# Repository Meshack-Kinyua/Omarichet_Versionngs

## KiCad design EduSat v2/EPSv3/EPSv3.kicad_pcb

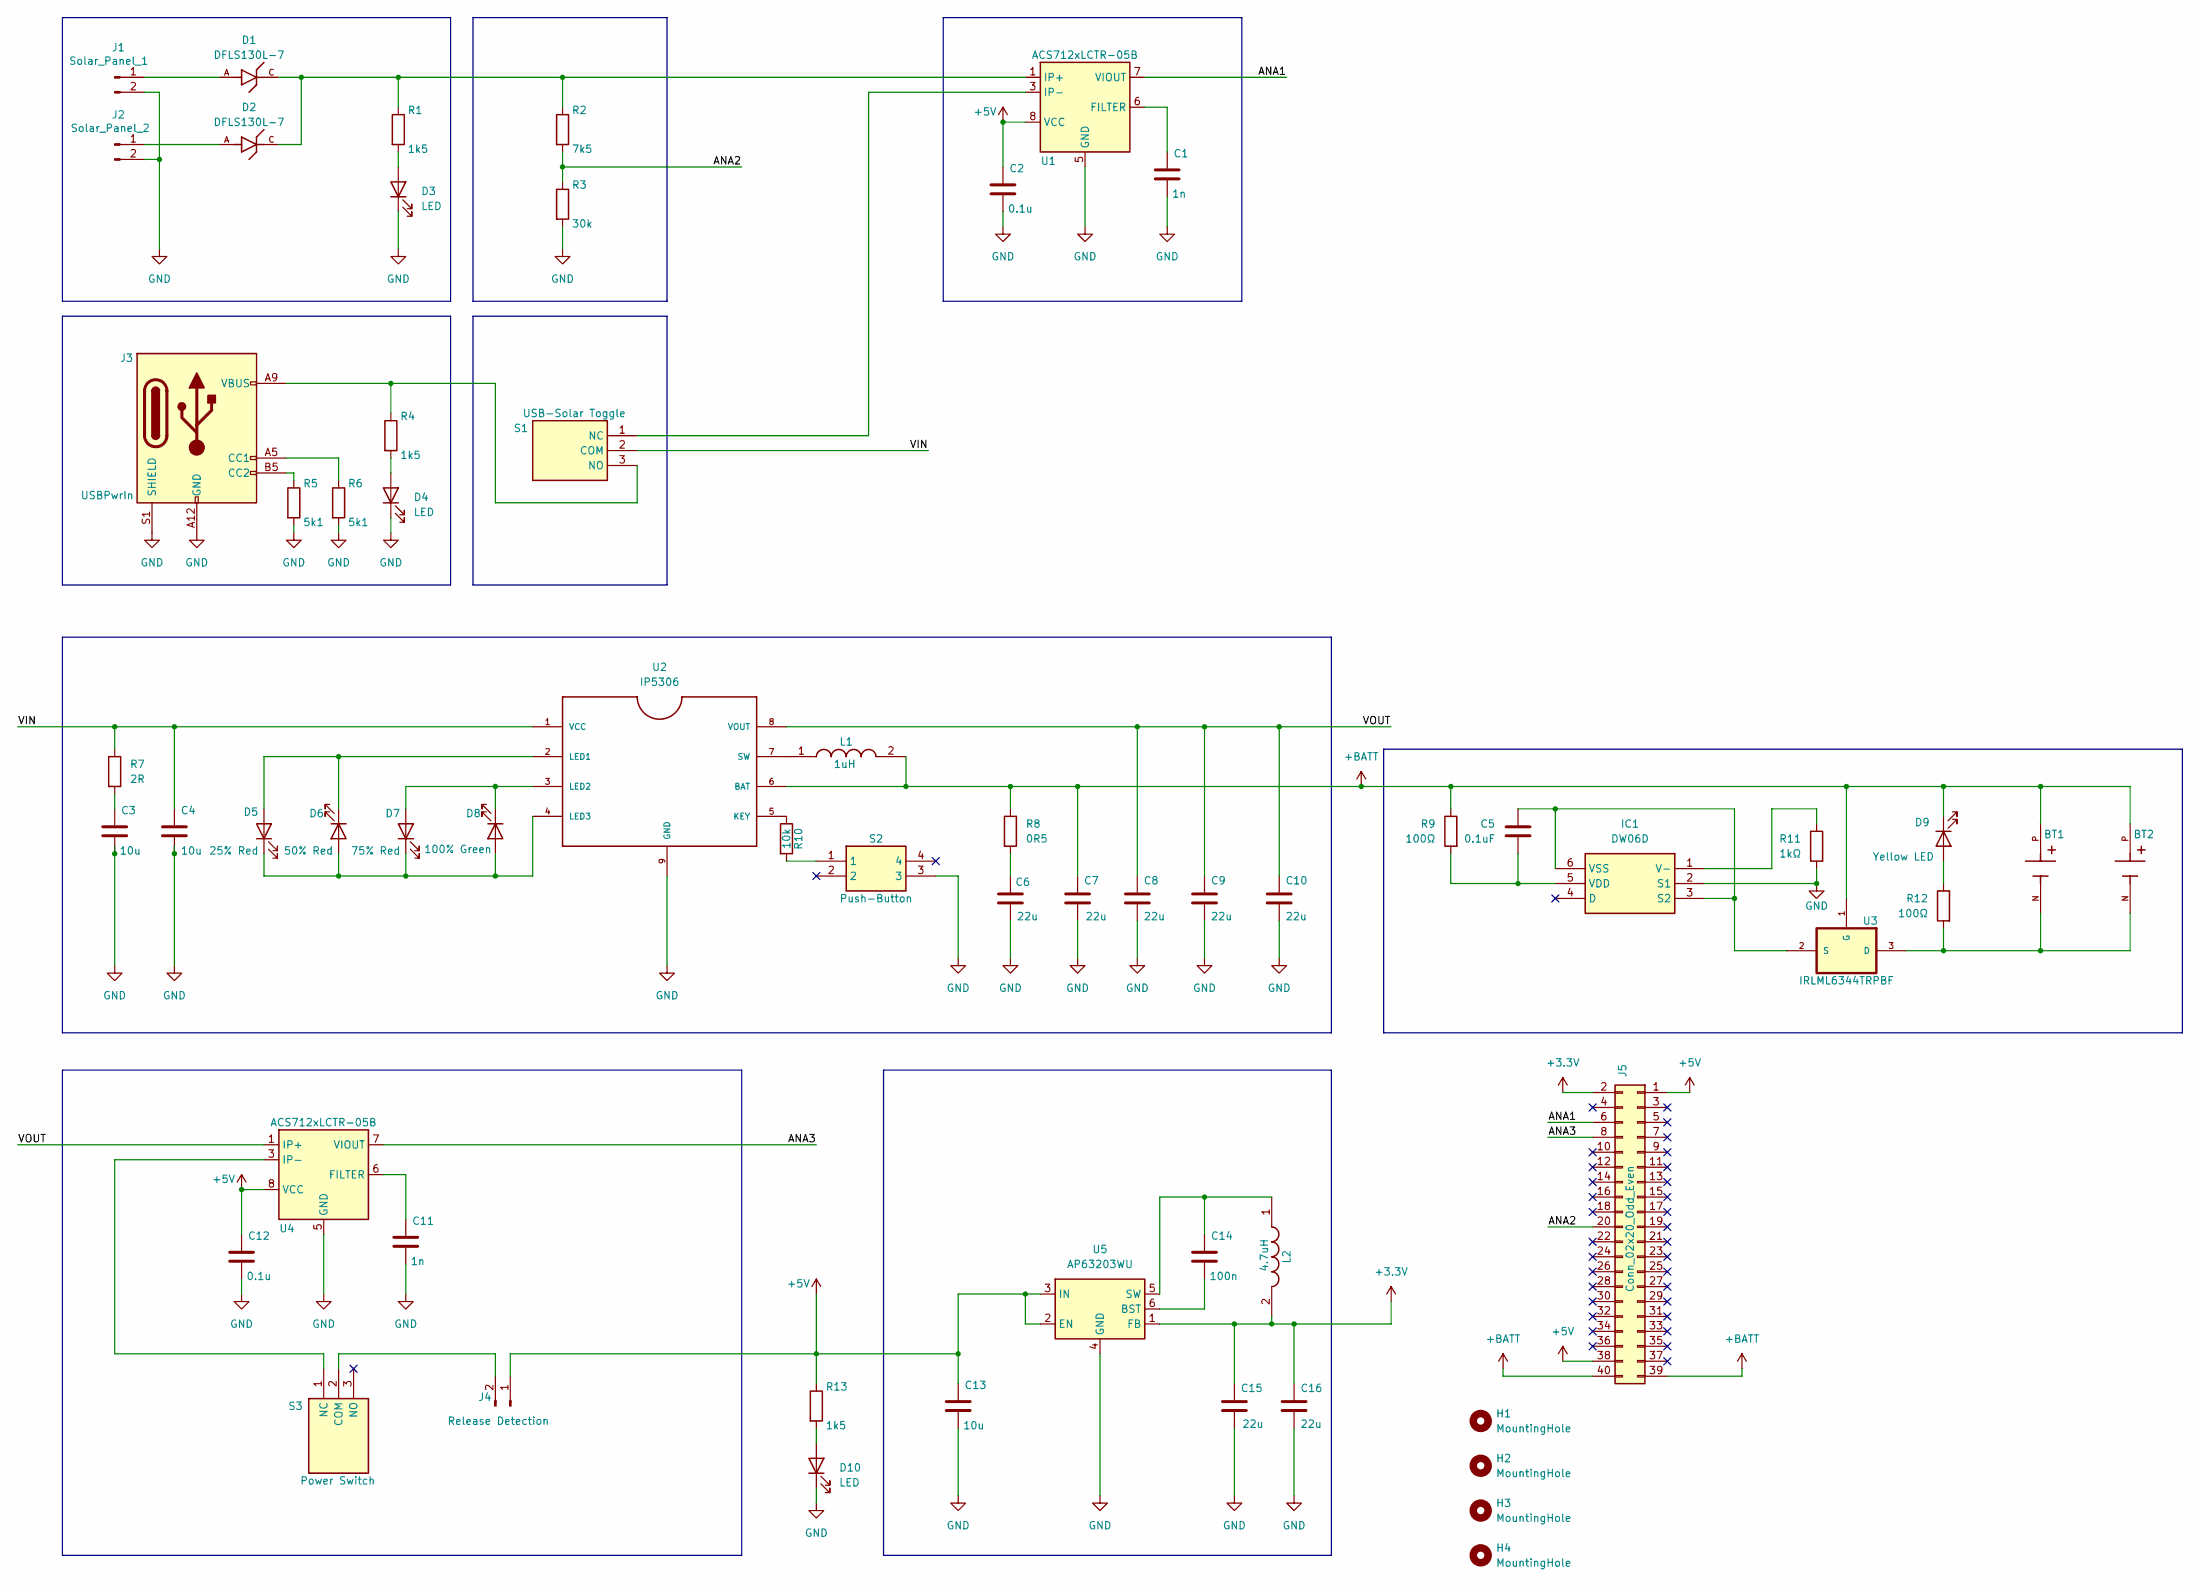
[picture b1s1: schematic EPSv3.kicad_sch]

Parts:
BT1, BT2: 1043; BAT_1043; PARTREV J
C1, C11: 1n; C_0805_2012Metric_Pad1.18x1.45mm_HandSolder
C2, C12: 0.1u; C_0805_2012Metric_Pad1.18x1.45mm_HandSolder
C3, C4, C13: 10u; C_0805_2012Metric_Pad1.18x1.45mm_HandSolder
C5: 0.1uF; C_0805_2012Metric_Pad1.18x1.45mm_HandSolder
C6, C7, C8, C9, C10, C15, C16: 22u; C_0805_2012Metric_Pad1.18x1.45mm_HandSolder
C14: 100n; C_0805_2012Metric_Pad1.18x1.45mm_HandSolder
D1, D2: DFLS130L-7; DIO_DFLS130L-7; PARTREV 5 - 2
D3, D4, D10: LED; LED_0805_2012Metric_Pad1.15x1.40mm_HandSolder
D5: 25% Red; LED_0805_2012Metric_Pad1.15x1.40mm_HandSolder
D6: 50% Red; LED_0805_2012Metric_Pad1.15x1.40mm_HandSolder
D7: 75% Red; LED_0805_2012Metric_Pad1.15x1.40mm_HandSolder
D8: 100% Green; LED_0805_2012Metric_Pad1.15x1.40mm_HandSolder
D9: Yellow LED; LED_0805_2012Metric_Pad1.15x1.40mm_HandSolder
H1, H2, H3, H4: MountingHole; MountingHole_3.2mm_M3
IC1: DW06D; DW06D_SFE; Manufacturer_Part_Number DW06D
J1: Solar_Panel_1; JST_XH_S2B-XH-A_1x02_P2.50mm_Horizontal
J2: Solar_Panel_2; JST_XH_S2B-XH-A_1x02_P2.50mm_Horizontal
J3: USBPwrIn; USB_C_Receptacle_GCT_USB4125-xx-x_6P_TopMnt_Horizontal
J4: Release Detection; JST_XH_S2B-XH-A_1x02_P2.50mm_Horizontal
J5: Conn_02x20_Odd_Even; PinSocket_2x20_P2.54mm_Vertical
L1: 1uH; INDPM7366X300N; Manufacturer_Part_Number MCS0630-100MN1
L2: 4.7uH; INDPM7366X300N; Manufacturer_Part_Number MCS0630-100MN1
R1, R4, R13: 1k5; R_0805_2012Metric_Pad1.20x1.40mm_HandSolder
R2: 7k5; R_0805_2012Metric_Pad1.20x1.40mm_HandSolder
R3: 30k; R_0805_2012Metric_Pad1.20x1.40mm_HandSolder
R5, R6: 5k1; R_0805_2012Metric_Pad1.20x1.40mm_HandSolder
R7: 2R; R_0805_2012Metric_Pad1.20x1.40mm_HandSolder
R8: 0R5; R_0805_2012Metric_Pad1.20x1.40mm_HandSolder
R9, R12: 100Ω; R_0805_2012Metric_Pad1.20x1.40mm_HandSolder
R10: 10k; R_0805_2012Metric_Pad1.20x1.40mm_HandSolder
R11: 1kΩ; R_0805_2012Metric_Pad1.20x1.40mm_HandSolder
S1: USB-Solar Toggle; SS12D10L3; Manufacturer_Part_Number SS-12D10L3
S2: Push-Button; PTS647SM50SMTR2LFS; Manufacturer_Part_Number PTS647SM50SMTR2LFS; Mouser Part Number 611-PTS647SM50SMTR2L
S3: Power Switch; SS12D10L3; Manufacturer_Part_Number SS-12D10L3
U1, U4: ACS712xLCTR-05B; SOIC-8_3.9x4.9mm_P1.27mm
U2: IP5306; SOIC9P127_490X600X170L84X42T330X241N
U3: IRLML6344TRPBF; SOT95P240X112-3N; MPN IRLML6344TRPBF
U5: AP63203WU; TSOT-23-6

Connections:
+3.3V: C15.1, C16.1, J5.2, L2.2, U5.1 (FB)
+5V: C2.1, C12.1, C13.1, J4.1, J5.1, J5.38, R13.1, U1.8 (VCC), U4.8 (VCC), U5.2 (EN), U5.3 (IN)
+BATT: BT1.P, BT2.P, C7.1, D9.1 (K), J5.39, J5.40, L1.2, R8.1, R9.1, U2.6 (BAT), U3.1 (G)
/ANA1: J5.6, U1.7 (VIOUT)
/ANA2: J5.20, R2.2, R3.1
/ANA3: J5.8, U4.7 (VIOUT)
/VIN: C4.1, R7.1, S1.2 (COM), U2.1 (VCC)
/VOUT: C8.1, C9.1, C10.1, U2.8 (VOUT), U4.1 (IP+), U4.2 (IP+)
GND: C1.2, C2.2, C3.2, C4.2, C6.2, C7.2, C8.2, C9.2, C10.2, C11.2, C12.2, C13.2, C15.2, C16.2, D3.1 (K), D4.1 (K), D10.1 (K), IC1.2 (S1), J1.2, J2.2, J3.A12 (GND), J3.B12 (GND), J3.S1 (SHIELD), R3.2, R5.2, R6.2, R11.2, S2.3, U1.5 (GND), U2.9 (GND), U4.5 (GND), U5.4 (GND)
unnamed: C3.1, R7.2
unnamed: C6.1, R8.2
unnamed: D1.C, D2.C, R1.1, R2.1, U1.1 (IP+), U1.2 (IP+)
unnamed: D3.2 (A), R1.2
unnamed: D4.2 (A), R4.2
unnamed: D5.2 (A), D6.1 (K), U2.2 (LED1)
unnamed: D5.1 (K), D6.2 (A), D7.1 (K), D8.2 (A), U2.4 (LED3)
unnamed: D7.2 (A), D8.1 (K), U2.3 (LED2)
unnamed: D9.2 (A), R12.1
unnamed: D10.2 (A), R13.2
unnamed: C5.1, IC1.3 (S2), IC1.6 (VSS), U3.2 (S)
unnamed: IC1.1 (V-), R11.1
unnamed: C5.2, IC1.5 (VDD), R9.2
unnamed: D1.A, J1.1
unnamed: D2.A, J2.1
unnamed: J3.A5 (CC1), R6.1
unnamed: J3.B5 (CC2), R5.1
unnamed: J4.2, S3.2 (COM)
unnamed: R10.2, S2.1
unnamed: S1.1 (NC), U1.3 (IP-), U1.4 (IP-)
unnamed: J3.A9 (VBUS), J3.B9 (VBUS), R4.1, S1.3 (NO)
unnamed: S3.1 (NC), U4.3 (IP-), U4.4 (IP-)
unnamed: C1.1, U1.6 (FILTER)
unnamed: R10.1, U2.5 (KEY)
unnamed: L1.1, U2.7 (SW)
unnamed: BT1.N, BT2.N, R12.2, U3.3 (D)
unnamed: C11.1, U4.6 (FILTER)
unnamed: C14.2, U5.6 (BST)
unnamed: C14.1, L2.1, U5.5 (SW)

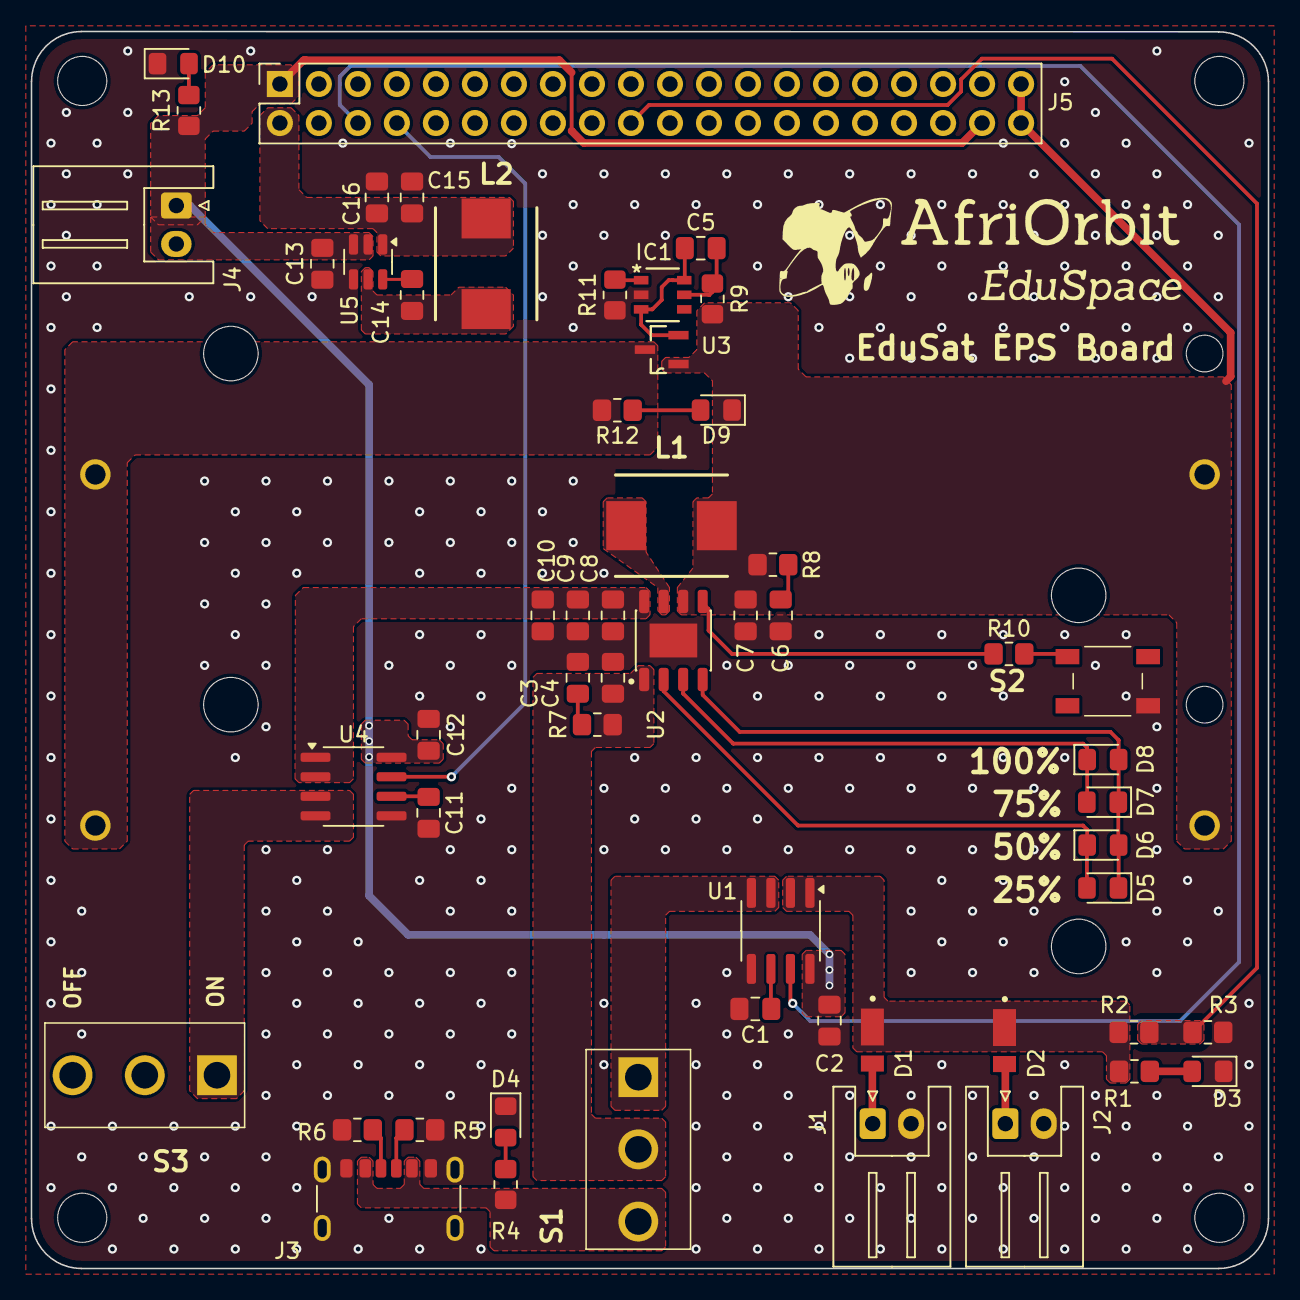
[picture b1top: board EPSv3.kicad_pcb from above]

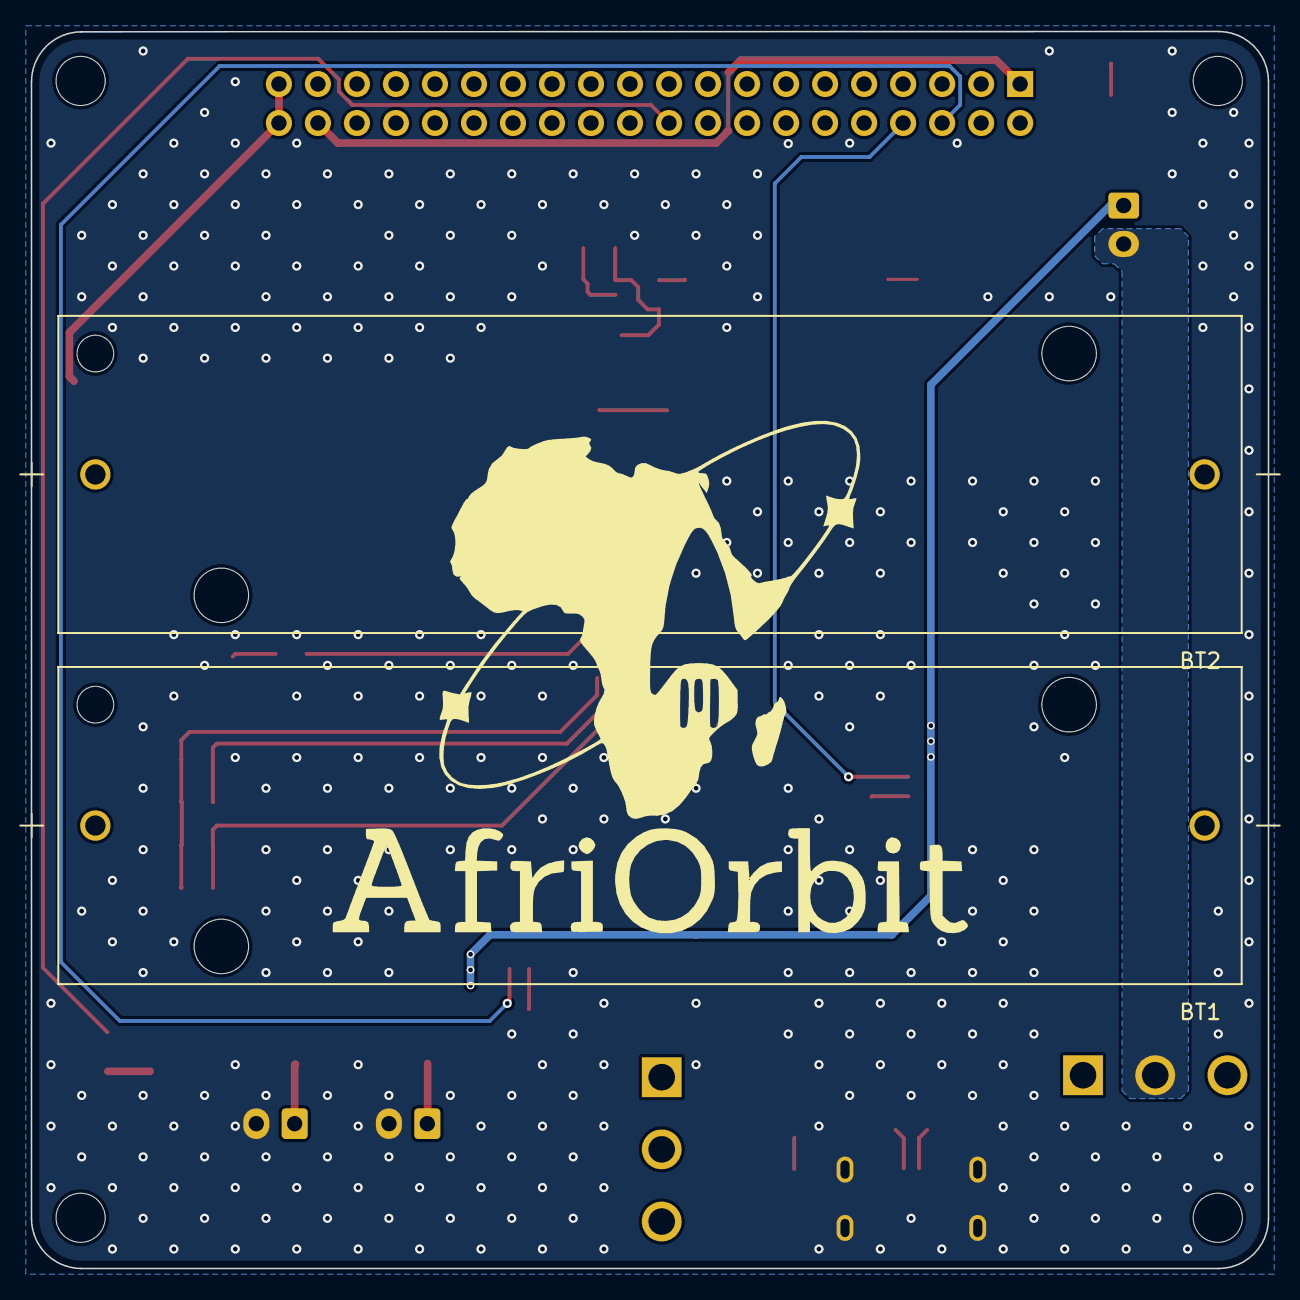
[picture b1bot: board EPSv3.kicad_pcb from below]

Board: 2 copper layers, 80.5 x 80.5 mm, 61 parts (2 on the bottom side), 38 nets.

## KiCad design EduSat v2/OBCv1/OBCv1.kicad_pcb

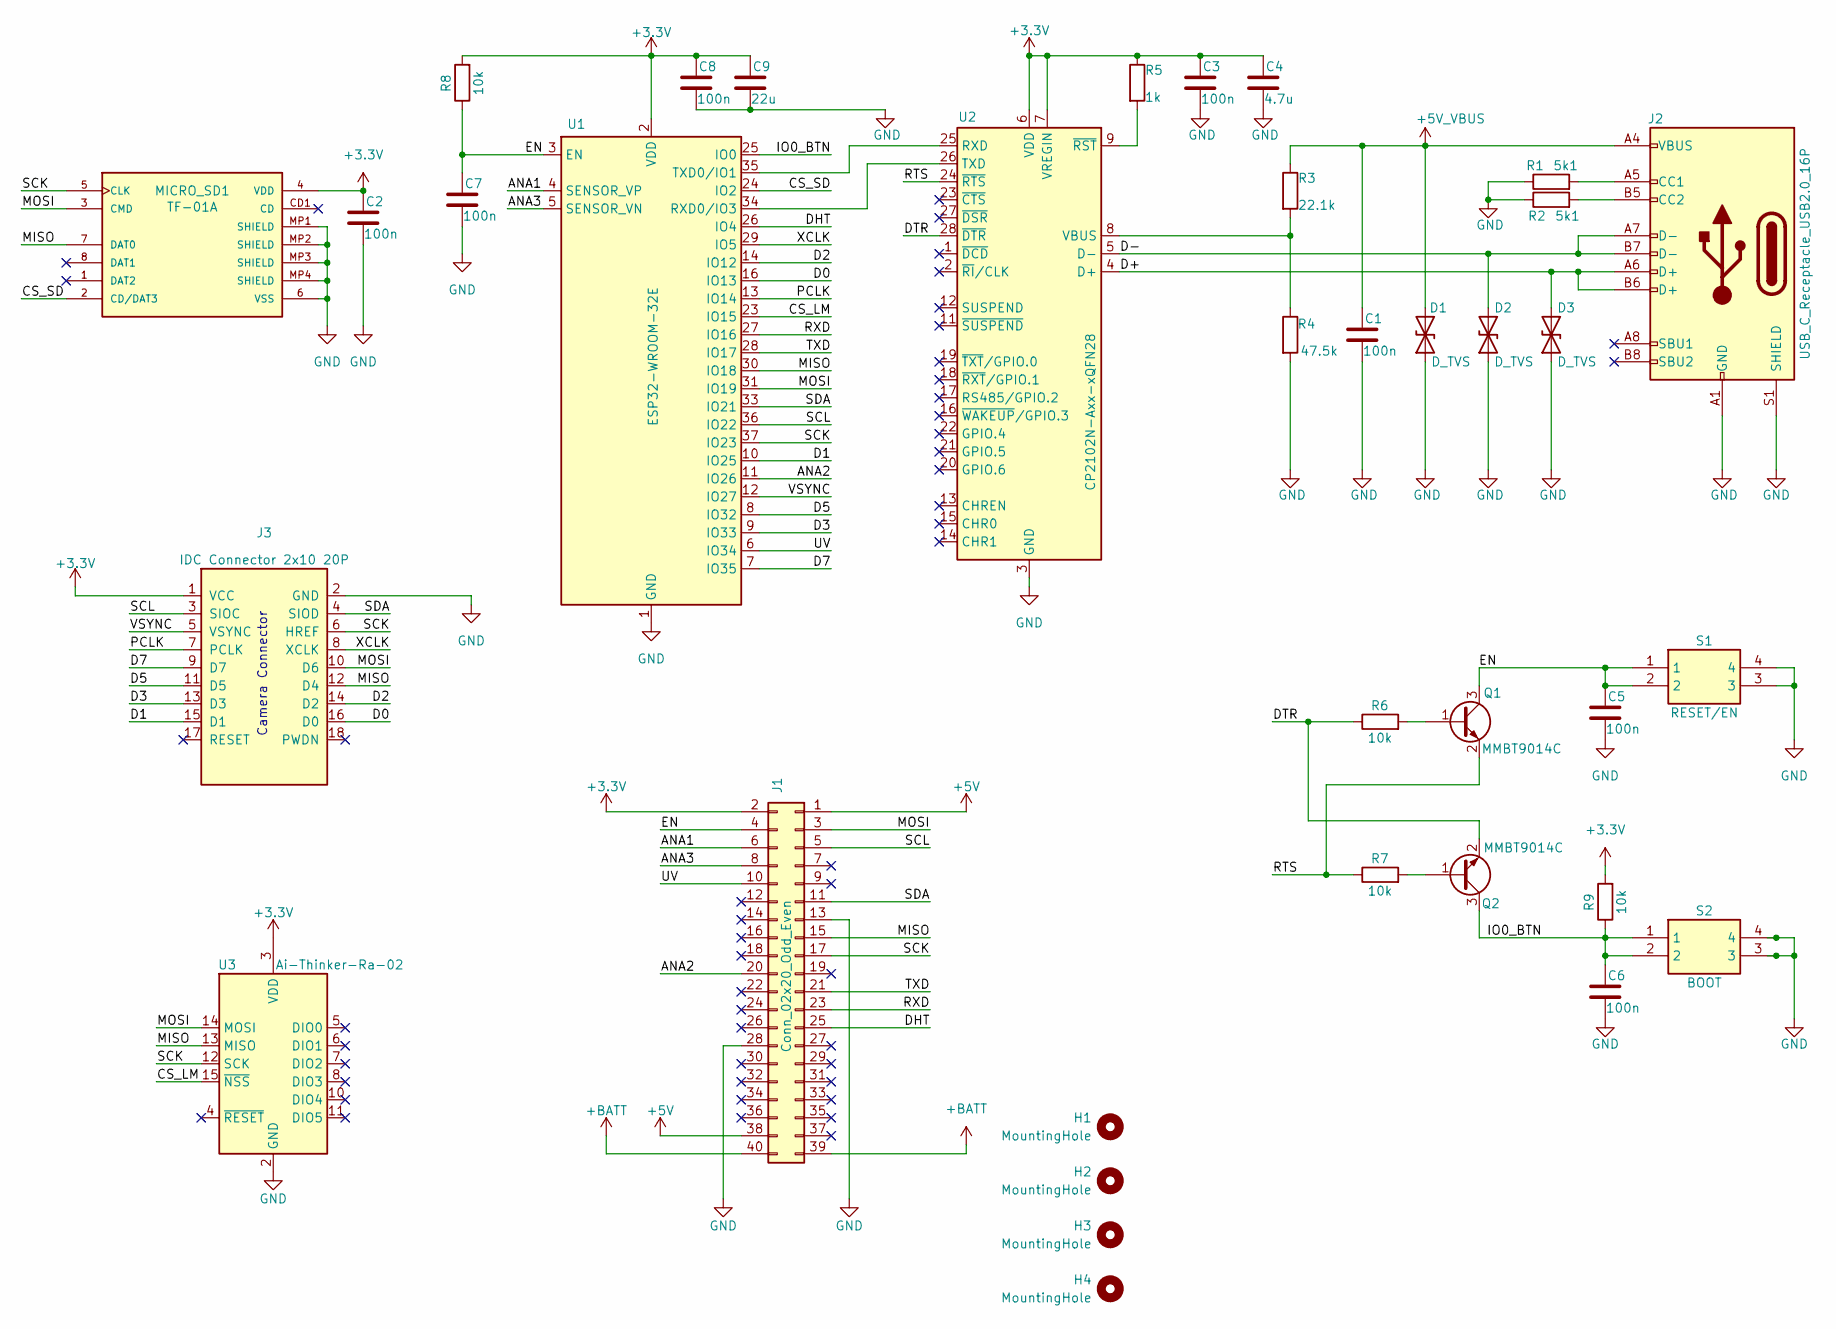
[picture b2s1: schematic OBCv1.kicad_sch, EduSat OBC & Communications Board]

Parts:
C1, C2, C3, C5, C6, C7, C8: 100n; C_0805_2012Metric
C4: 4.7u; C_0805_2012Metric
C9: 22u; C_0805_2012Metric
D1, D2, D3: D_TVS; D_0603_1608Metric
H1, H2, H3, H4: MountingHole; MountingHole_3.2mm_M3
J1: Conn_02x20_Odd_Even; PinSocket_2x20_P2.54mm_Vertical
J2: USB_C_Receptacle_USB2.0_16P; USB_C_Receptacle_XKB_U262-16XN-4BVC11
J3: IDC Connector 2x10 20P; IDC-Header_2x10_P2.54mm_Horizontal
MICRO_SD1: TF-01A
Q1, Q2: MMBT9014C; SOT-23
R1, R2: 5k1; R_0805_2012Metric
R3: 22.1k; R_0805_2012Metric_Pad1.20x1.40mm_HandSolder
R4: 47.5k; R_0805_2012Metric_Pad1.20x1.40mm_HandSolder
R5: 1k; R_0805_2012Metric_Pad1.20x1.40mm_HandSolder
R6, R7, R8, R9: 10k; R_0805_2012Metric_Pad1.20x1.40mm_HandSolder
S1: RESET/EN; PTS647SM50SMTR2LFS; Manufacturer_Part_Number PTS647SM50SMTR2LFS; Mouser Part Number 611-PTS647SM50SMTR2L
S2: BOOT; PTS647SM50SMTR2LFS; Manufacturer_Part_Number PTS647SM50SMTR2LFS; Mouser Part Number 611-PTS647SM50SMTR2L
U1: ESP32-WROOM-32E; ESP32-WROOM-32D
U2: CP2102N-Axx-xQFN28; QFN-28-1EP_5x5mm_P0.5mm_EP3.35x3.35mm
U3: Ai-Thinker-Ra-02; Ai-Thinker-Ra-01-LoRa

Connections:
+3.3V: C2.1, C3.1, C4.1, C8.1, C9.1, J1.2, J3.1 (VCC), MICRO_SD1.4 (VDD), R5.1, R8.2, R9.2, U1.2 (VDD), U2.6 (VDD), U2.7 (VREGIN), U3.3 (VDD)
+5V: J1.1, J1.38
+5V_VBUS: C1.1, D1.2 (A2), J2.A4 (VBUS), J2.A9 (VBUS), J2.B4 (VBUS), J2.B9 (VBUS), R3.1
+BATT: J1.39, J1.40
/ANA1: J1.6, U1.4 (SENSOR_VP)
/ANA2: J1.20, U1.11 (IO26)
/ANA3: J1.8, U1.5 (SENSOR_VN)
/CS_LM: U1.23 (IO15), U3.15 (~NSS)
/CS_SD: MICRO_SD1.2 (CD/DAT3), U1.24 (IO2)
/D0: J3.16 (D0), U1.16 (IO13)
/D1: J3.15 (D1), U1.10 (IO25)
/D2: J3.14 (D2), U1.14 (IO12)
/D3: J3.13 (D3), U1.9 (IO33)
/D5: J3.11 (D5), U1.8 (IO32)
/D7: J3.9 (D7), U1.7 (IO35)
/D+: D3.2 (A2), J2.A6 (D+), J2.B6 (D+), U2.4 (D+)
/D-: D2.2 (A2), J2.A7 (D-), J2.B7 (D-), U2.5 (D-)
/DHT: J1.25, U1.26 (IO4)
/DTR: Q2.2 (E), R6.1, U2.28 (~DTR)
/EN: C5.1, C7.1, J1.4, Q1.3 (C), R8.1, S1.1, S1.2, U1.3 (EN)
/IO0_BTN: C6.1, Q2.3 (C), R9.1, S2.1, S2.2, U1.25 (IO0)
/MISO: J1.15, J3.12 (D4), MICRO_SD1.7 (DAT0), U1.30 (IO18), U3.13 (MISO)
/MOSI: J1.3, J3.10 (D6), MICRO_SD1.3 (CMD), U1.31 (IO19), U3.14 (MOSI)
/PCLK: J3.7 (PCLK), U1.13 (IO14)
/RTS: Q1.2 (E), R7.1, U2.24 (~RTS)
/RXD: J1.23, U1.27 (IO16)
/SCK: J1.17, J3.6 (HREF), MICRO_SD1.5 (CLK), U1.37 (IO23), U3.12 (SCK)
/SCL: J1.5, J3.3 (SIOC), U1.36 (IO22)
/SDA: J1.11, J3.4 (SIOD), U1.33 (IO21)
/TXD: J1.21, U1.28 (IO17)
/UV: J1.10, U1.6 (IO34)
/VSYNC: J3.5 (VSYNC), U1.12 (IO27)
/XCLK: J3.8 (XCLK), U1.29 (IO5)
GND: C1.2, C2.2, C3.2, C4.2, C5.2, C6.2, C7.2, C8.2, C9.2, D1.1 (A1), D2.1 (A1), D3.1 (A1), J1.13, J1.28, J2.A1 (GND), J2.A12 (GND), J2.B1 (GND), J2.B12 (GND), J2.S1 (SHIELD), J3.2 (GND), MICRO_SD1.6 (VSS), MICRO_SD1.MP1 (SHIELD), MICRO_SD1.MP2 (SHIELD), MICRO_SD1.MP3 (SHIELD), MICRO_SD1.MP4 (SHIELD), R1.1, R2.1, R4.2, S1.3, S1.4, S2.3, S2.4, U1.1 (GND), U1.15 (GND), U1.38 (GND), U1.39 (GND), U2.3 (GND), U2.29 (GND), U3.1 (GND), U3.2 (GND), U3.9 (GND), U3.16 (GND)
unnamed: J2.A5 (CC1), R1.2
unnamed: J2.B5 (CC2), R2.2
unnamed: Q1.1 (B), R6.2
unnamed: Q2.1 (B), R7.2
unnamed: U1.34 (RXD0/IO3), U2.26 (TXD)
unnamed: U1.35 (TXD0/IO1), U2.25 (RXD)
unnamed: R3.2, R4.1, U2.8 (VBUS)
unnamed: R5.2, U2.9 (~RST)

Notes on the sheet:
Camera Connector

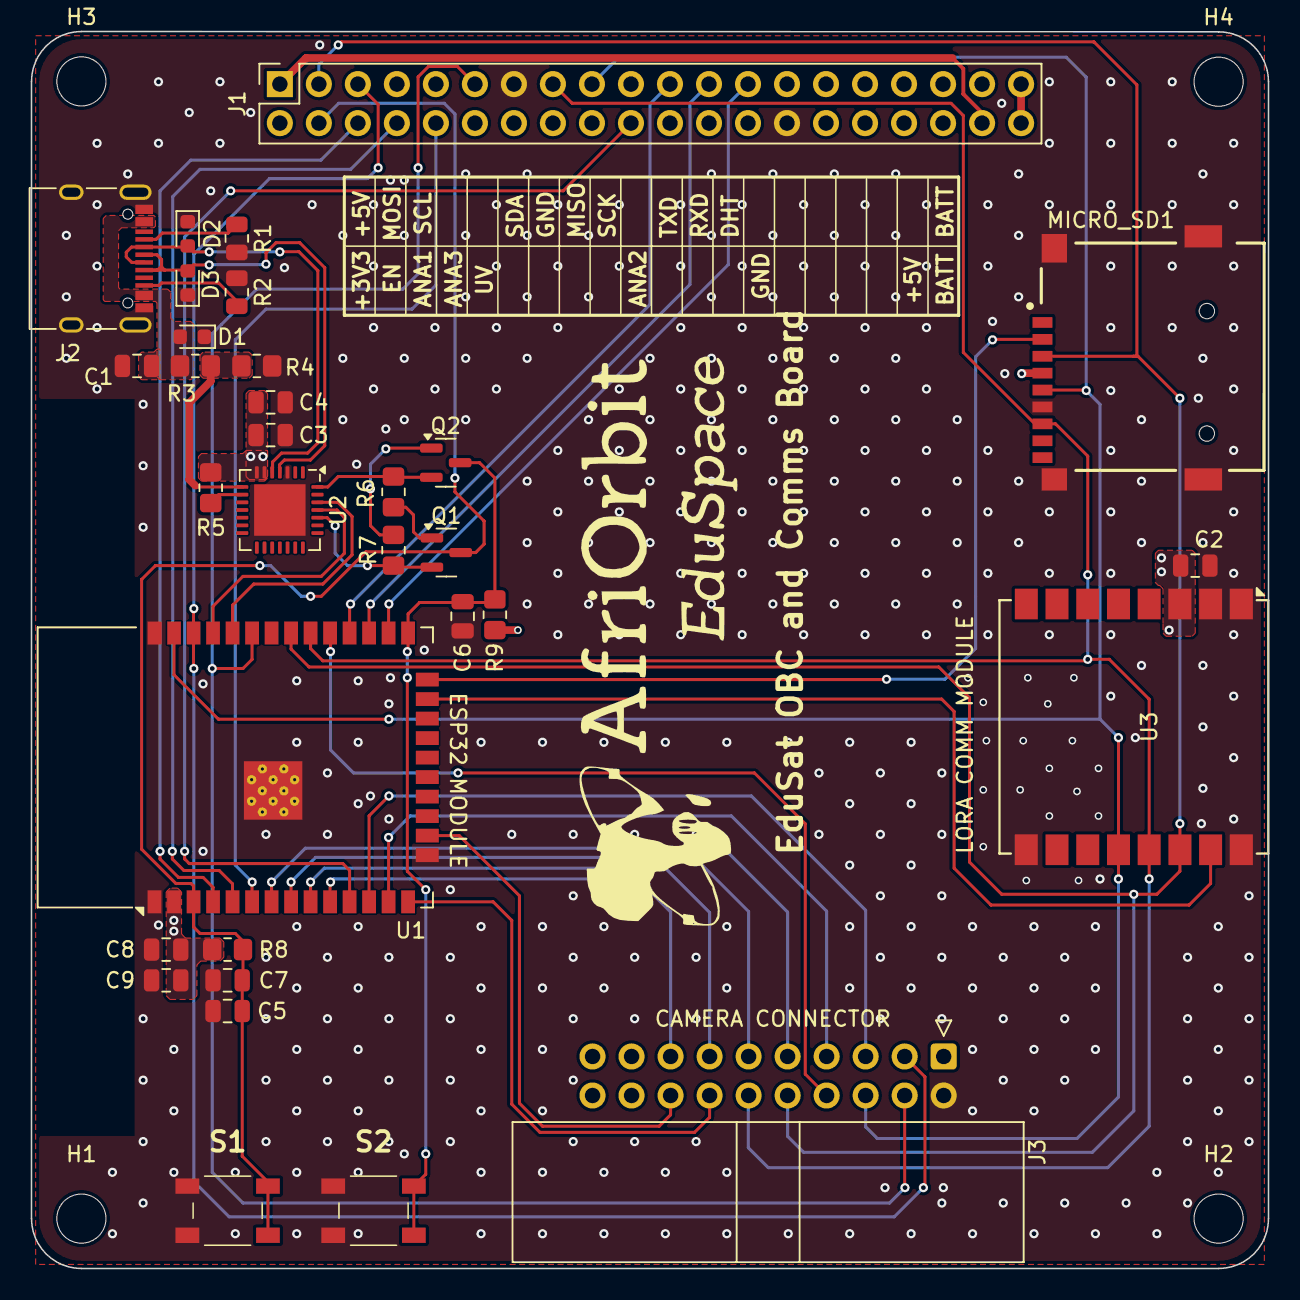
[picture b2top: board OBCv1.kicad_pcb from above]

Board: 4 copper layers, 80.5 x 80.5 mm, 36 parts (0 on the bottom side), 42 nets.

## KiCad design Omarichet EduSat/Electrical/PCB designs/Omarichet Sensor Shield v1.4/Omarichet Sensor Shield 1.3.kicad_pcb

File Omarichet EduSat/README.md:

# School-Edusat

The project aims to create an open-source High School Level Satellite Space Education Project for STEAM education - based on HEPTA-Sat Training.

The project will be divided into 8 x 2-hour workshop trainings running on a low-cost processor.

2 possible configurations and scenarios will be considered:

1) Student has a laptop - will use Arduino MCU.
2) Student has no laptop - will use and run entire project on Raspberry Pi.

For compatibility and uniformity of curriculum, and to concentrate on building in C language, run Arduino sketches on Pi https://www.deviceplus.com/raspberry-pi/how-to-run-arduino-sketches-on-raspberry-pi/

## _A. Mission Design_
#### 1. Lesson Objectives
- Determine the mission theme from user needs.
- Determine mission requirements through mission goal statements.
- Define mission success criteria and verification methods.
- Conduct schedule, cost, and risk planning.
- Select On-Board Computer (OBC) processor based on the mission and criteria such as cost, clock speed, etc. 
- Establish how to interface the OBC with a computer for feeding commands and testing.

#### 2. Materials Required
- OBC Management Software (e.g. mbed, Raspbian NOOBS, etc.)

## _B. Power System_
#### 1. Lesson Objectives
- Understand the components and functions of an Electric Power System (EPS) e.g. power generation, charge control, etc.
- Understand EPS architecture to suit above functions (how connections are made, pin assignment, etc.)
- Determine power consumption levels of on-board equipment, among other factors, to enable selection of suitable EPS components.
- Establish verification methods and measures.

#### 2. Materials Required
- Solar Array.
- Battery.
- Charge controller.
- Step-up (or Step-Down) converter.
- Flight pin(s)/Release Detection Switch(es).
- EPS board.

## _C. Command Subsystem_
#### 1. Lesson Objectives
- Describe the components and functions of the Command and Data Handling (C&DH) subsystem.
- Establish criteria for selecting components based on mission requirements.
- Understand command and telemetry data structure. 

#### 2. Materials Required
- C&DH Board

## _D. Sensors Subsystem_
#### 1. Lesson Objectives
- Describe subsystem requirements according to mission theme.
- Describe subsystem components and functions (architecture).
- Define housekeeping (HK) data.
- Establish criteria for selecting sensors and other components.
- Introduce and explain the concept of Attitude Determination and Control.
- Establish verification measures such as receiving HK data from sensors.
- Establish selection criteria for the camera based on factors such as size, resolution, etc.
- Determine verification measures and methods such as taking a photo. 
- Synchronizing the camera to the OBC.

#### 2. Materials Required
- 9-axis sensor.
- Actuators such as reaction wheels, cold gas jets, magnetic torquers, etc. depending on mission requirements among other criteria such as availability, cost, etc. 
- GPS Receiver.
- Camera module.
- Sensors and communication board..

## _E. Ground System and Communication_
#### 1. Lesson Objectives
- Understand the components and functions of the communication and ground station subsystems.
- Define the interdependent relationship between the ground station subsystem and the on-board communication subsystem.
- Understand the function of communication and ground station subsystems in changing a satellite's status e.g. ON/OFF, operational mode, etc. 
- Establish wireless communication between the subsystems by understanding their architecture. 
- Establish criteria for component selection.
- Describe how to set up the XBee modules using XCTU software.
- Determine verification measures and methods. 

#### 2. Materials Required
- Receiving and transmitting antennae.
- XBee transmitter and receiver modules.
- XBee USB dongle.
- Downlink and uplink software. 

## _F. Mechanical Design_
#### 1. Lesson Objectives
- Download and install OpenSCAD software from the official site. (Both Windows and Raspberry Pi).
- Introduce OpenSCAD by learning how it works (basic functions and commands).  

      A. Creating new files.
      B. Defining basic shapes (cubes, cylinders, etc.) and their position on the XYZ-plane. 
- Test understanding by using OpenSCAD to design the solar cell jig or battery jig.  

      A. Introduce commands such as union, intersection, and difference. 
      B. Use functions such as translate  and rotate to orient shapes on the plane.
- Describe how to export the 3-D designs (.stl files) to the 3-D printer using Creality Slicer (or other slicer software).
- Display the provided CubeSat designs on Creality Slicer for printing.

#### 2. Materials Required
- 3-D Printer.
- OpenSCAD software.
- Creality Slicer software.

## _G. Final Assembly and Test_
#### 1. Lesson Objectives
- Connect all EPS components to the EPS board and install spacers.
- Connect all C&DH components to the C&DH board and install spacers.
- Connect all required sensors and communication devices to the sensor and communication board and install spacers.

#### 2. Materials Required
- All parts and materials from previous sections.
- CubeSat analysis software (e.g. Flip360 or Fusion360).

## _H. Party Balloon Launch_

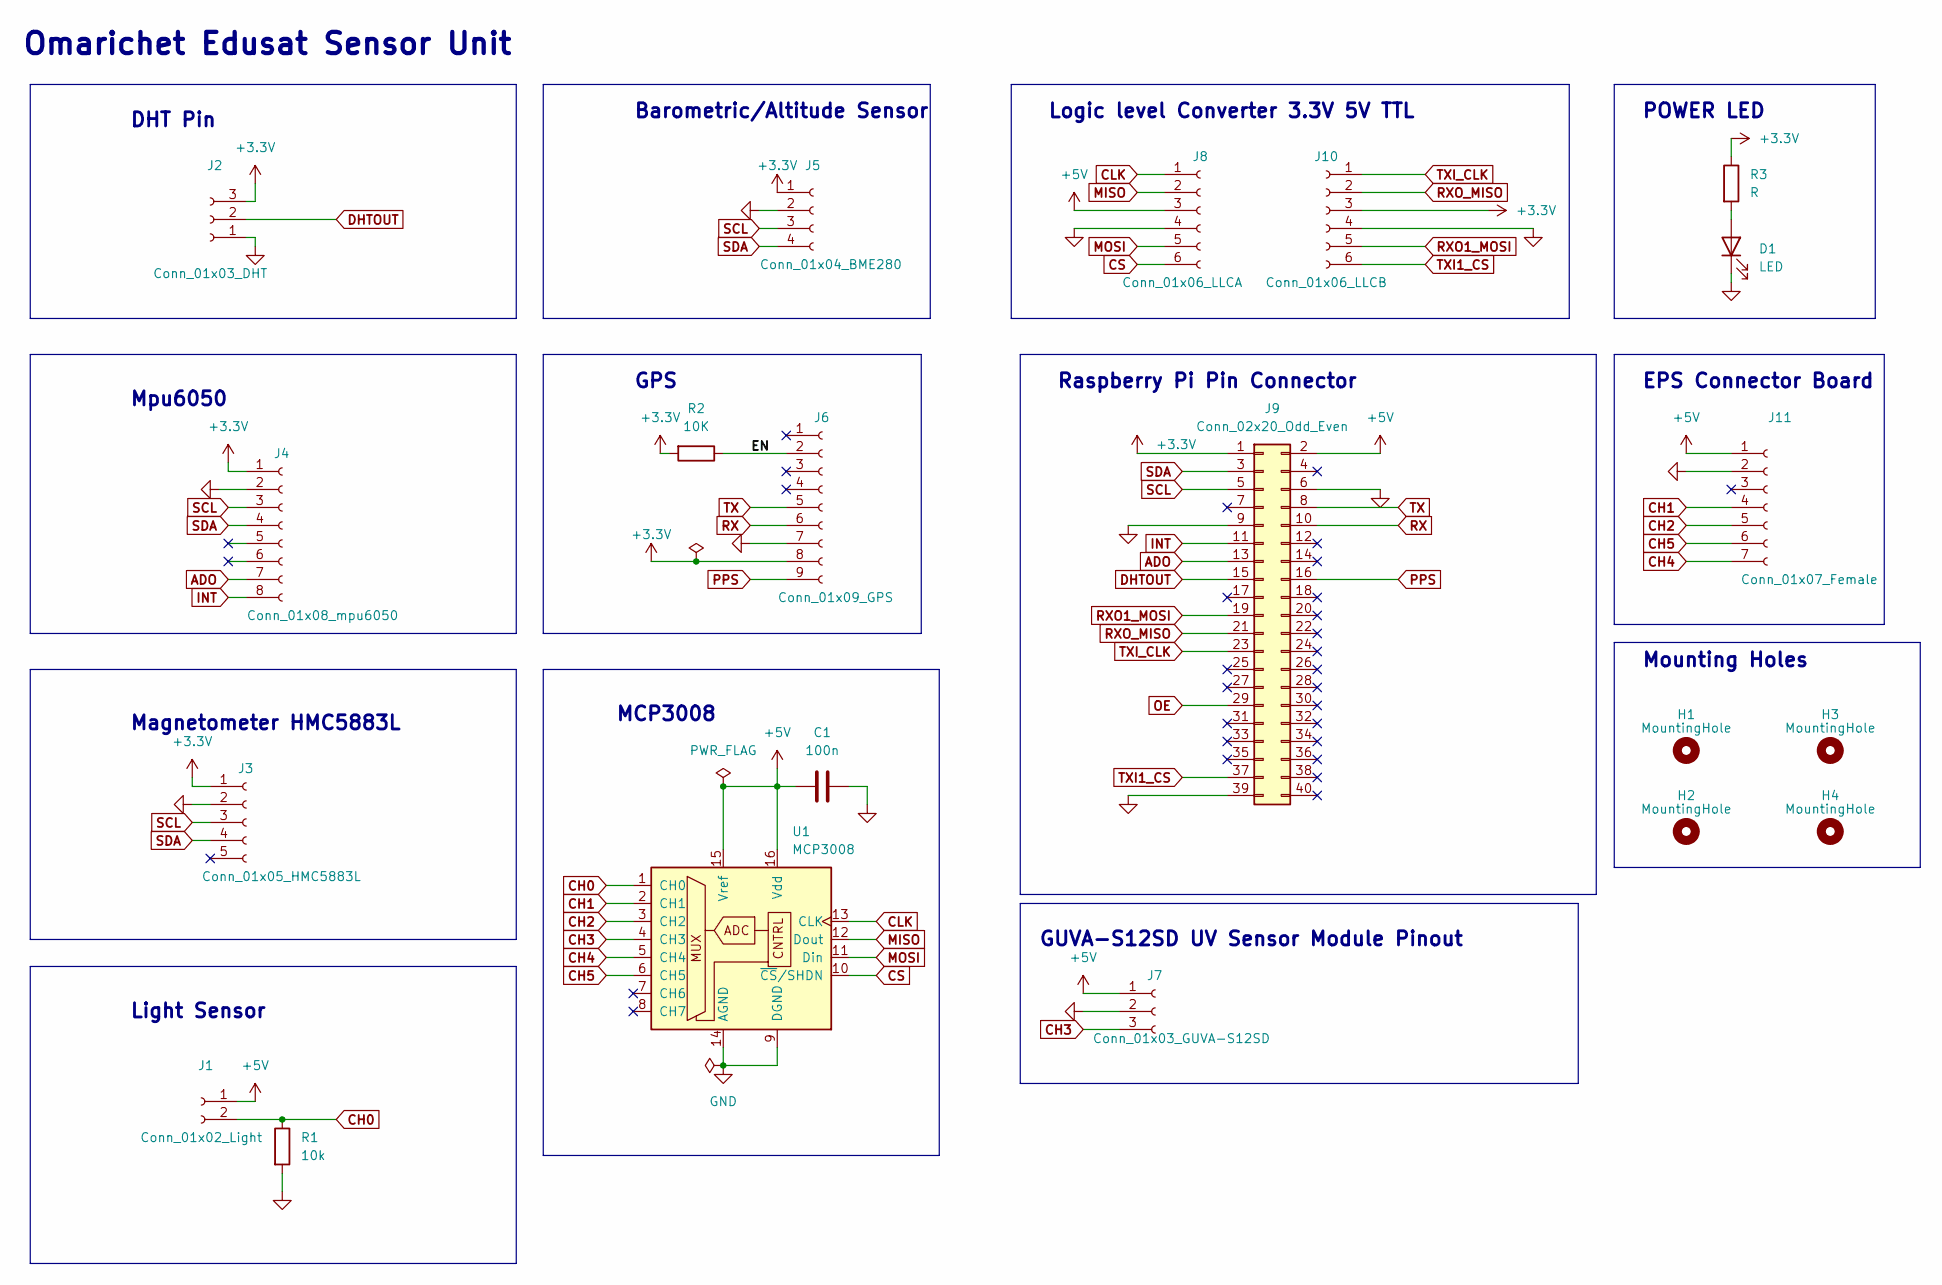
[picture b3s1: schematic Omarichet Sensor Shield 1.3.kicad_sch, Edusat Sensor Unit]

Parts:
C1: 100n; C_0805_2012Metric
D1: LED; LED_0805_2012Metric
H1, H2, H3, H4: MountingHole; MountingHole_3.2mm_M3
J1: Conn_01x02_Light; PinSocket_1x02_P2.54mm_Vertical
J2: Conn_01x03_DHT; PinSocket_1x03_P2.54mm_Vertical
J3: Conn_01x05_HMC5883L; PinSocket_1x05_P2.54mm_Vertical
J4: Conn_01x08_mpu6050; PinSocket_1x08_P2.54mm_Vertical
J5: Conn_01x04_BME280; PinSocket_1x04_P2.54mm_Vertical
J6: Conn_01x09_GPS; PinSocket_1x09_P2.54mm_Vertical
J7: Conn_01x03_GUVA-S12SD; PinSocket_1x03_P2.54mm_Vertical
J8: Conn_01x06_LLCA; PinSocket_1x06_P2.54mm_Vertical
J9: Conn_02x20_Odd_Even; PinSocket_2x20_P2.54mm_Vertical
J10: Conn_01x06_LLCB; PinSocket_1x06_P2.54mm_Vertical
J11: Conn_01x07_Female; PinSocket_1x07_P2.54mm_Vertical
R1: 10k; R_0603_1608Metric
R2: 10K; R_0603_1608Metric
R3: R; R_0603_1608Metric
U1: MCP3008; DIP-16_W7.62mm

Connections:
+3.3V: J2.3, J3.1, J4.1, J5.1, J6.8, J9.1, J10.3, R2.2, R3.1
+5V: C1.1, J1.1, J7.1, J8.3, J9.2, J11.1, U1.15 (Vref), U1.16 (Vdd)
/EN: J6.2, R2.1
ADO: J4.7, J9.13
CH0: J1.2, R1.1, U1.1 (CH0)
CH1: J11.4, U1.2 (CH1)
CH2: J11.5, U1.3 (CH2)
CH3: J7.3, U1.4 (CH3)
CH4: J11.7, U1.5 (CH4)
CH5: J11.6, U1.6 (CH5)
CLK: J8.1, U1.13 (CLK)
CS: J8.6, U1.10 (~CS/SHDN)
DHTOUT: J2.2, J9.15
GND: C1.2, D1.1 (K), J2.1, J3.2, J4.2, J5.2, J6.7, J7.2, J8.4, J9.6, J9.9, J9.39, J10.4, J11.2, R1.2, U1.9 (DGND), U1.14 (AGND)
INT: J4.8, J9.11
MISO: J8.2, U1.12 (Dout)
MOSI: J8.5, U1.11 (Din)
unnamed: D1.2 (A), R3.2
OE: J9.29
PPS: J6.9, J9.16
RX: J6.6, J9.10
RXO1_MOSI: J9.19, J10.5
RXO_MISO: J9.21, J10.2
SCL: J3.3, J4.3, J5.3, J9.5
SDA: J3.4, J4.4, J5.4, J9.3
TX: J6.5, J9.8
TXI1_CS: J9.37, J10.6
TXI_CLK: J9.23, J10.1

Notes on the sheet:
Light Sensor
Omarichet Edusat Sensor Unit
GUVA-S12SD UV Sensor Module Pinout
POWER LED
GPS
MCP3008
Barometric/Altitude Sensor
Mpu6050
Raspberry Pi Pin Connector
Logic level Converter 3.3V 5V TTL
Magnetometer HMC5883L
EPS Connector Board
Mounting Holes
DHT Pin
